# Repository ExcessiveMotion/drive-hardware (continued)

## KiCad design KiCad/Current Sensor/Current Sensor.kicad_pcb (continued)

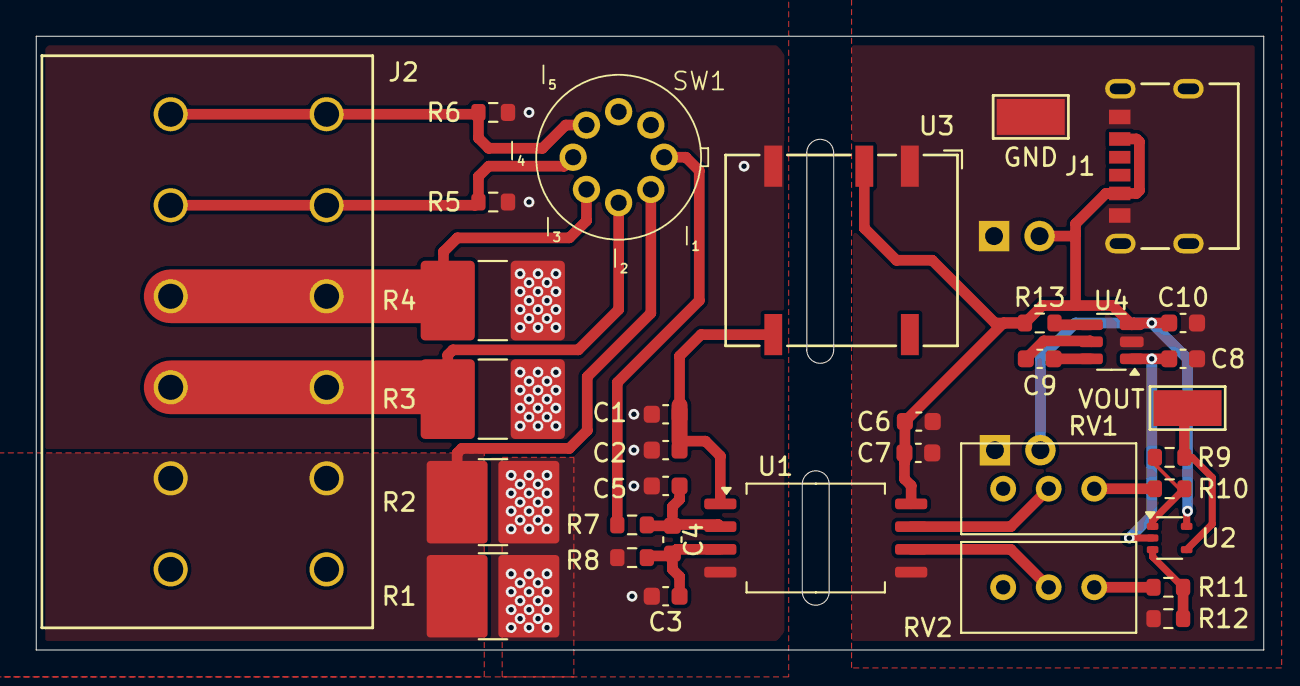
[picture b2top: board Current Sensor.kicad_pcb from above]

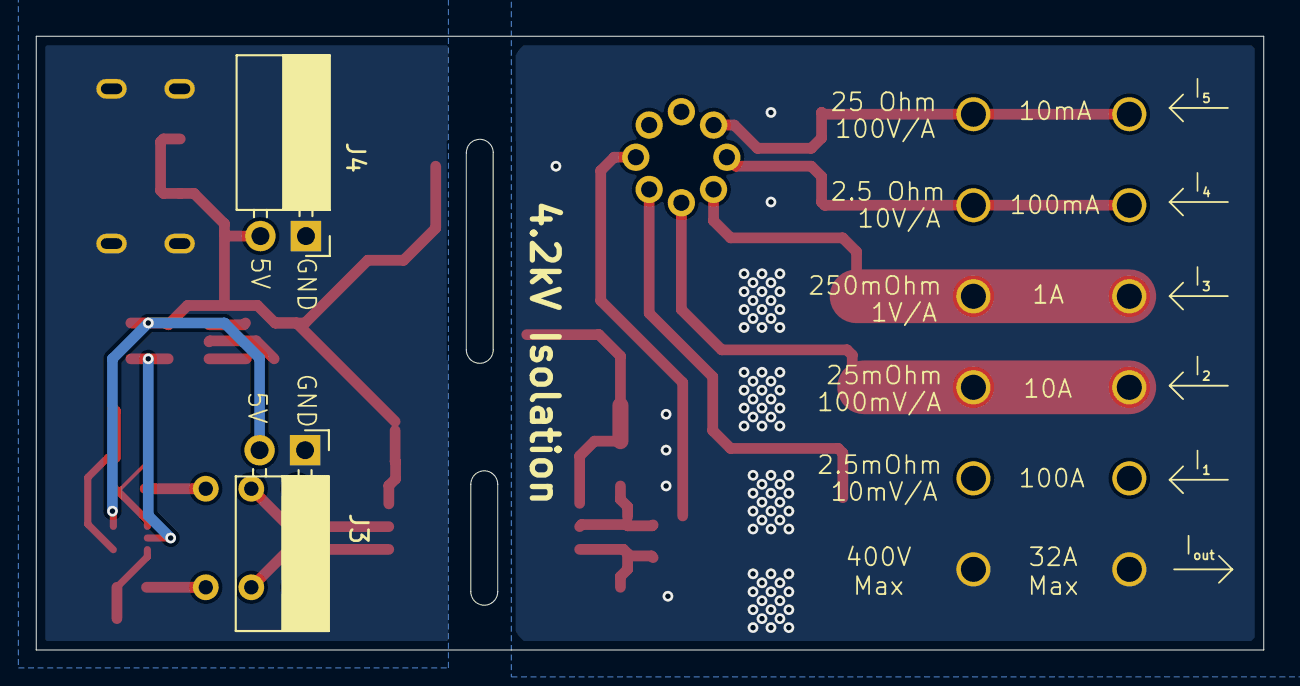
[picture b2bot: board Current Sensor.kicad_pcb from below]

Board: 2 copper layers, 68.5 x 34.2 mm, 36 parts (2 on the bottom side), 23 nets.

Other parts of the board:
GND: TestPoint_Keystone_5019_Minature
J3, J4: PinSocket_1x02_P2.54mm_Horizontal
VOUT: TestPoint_Keystone_5019_Minature

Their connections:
+5V: J3.2, J4.2; also elsewhere on the board
GND2: GND.1, J3.1, J4.1; also elsewhere on the board
VOUT: VOUT.1; also elsewhere on the board

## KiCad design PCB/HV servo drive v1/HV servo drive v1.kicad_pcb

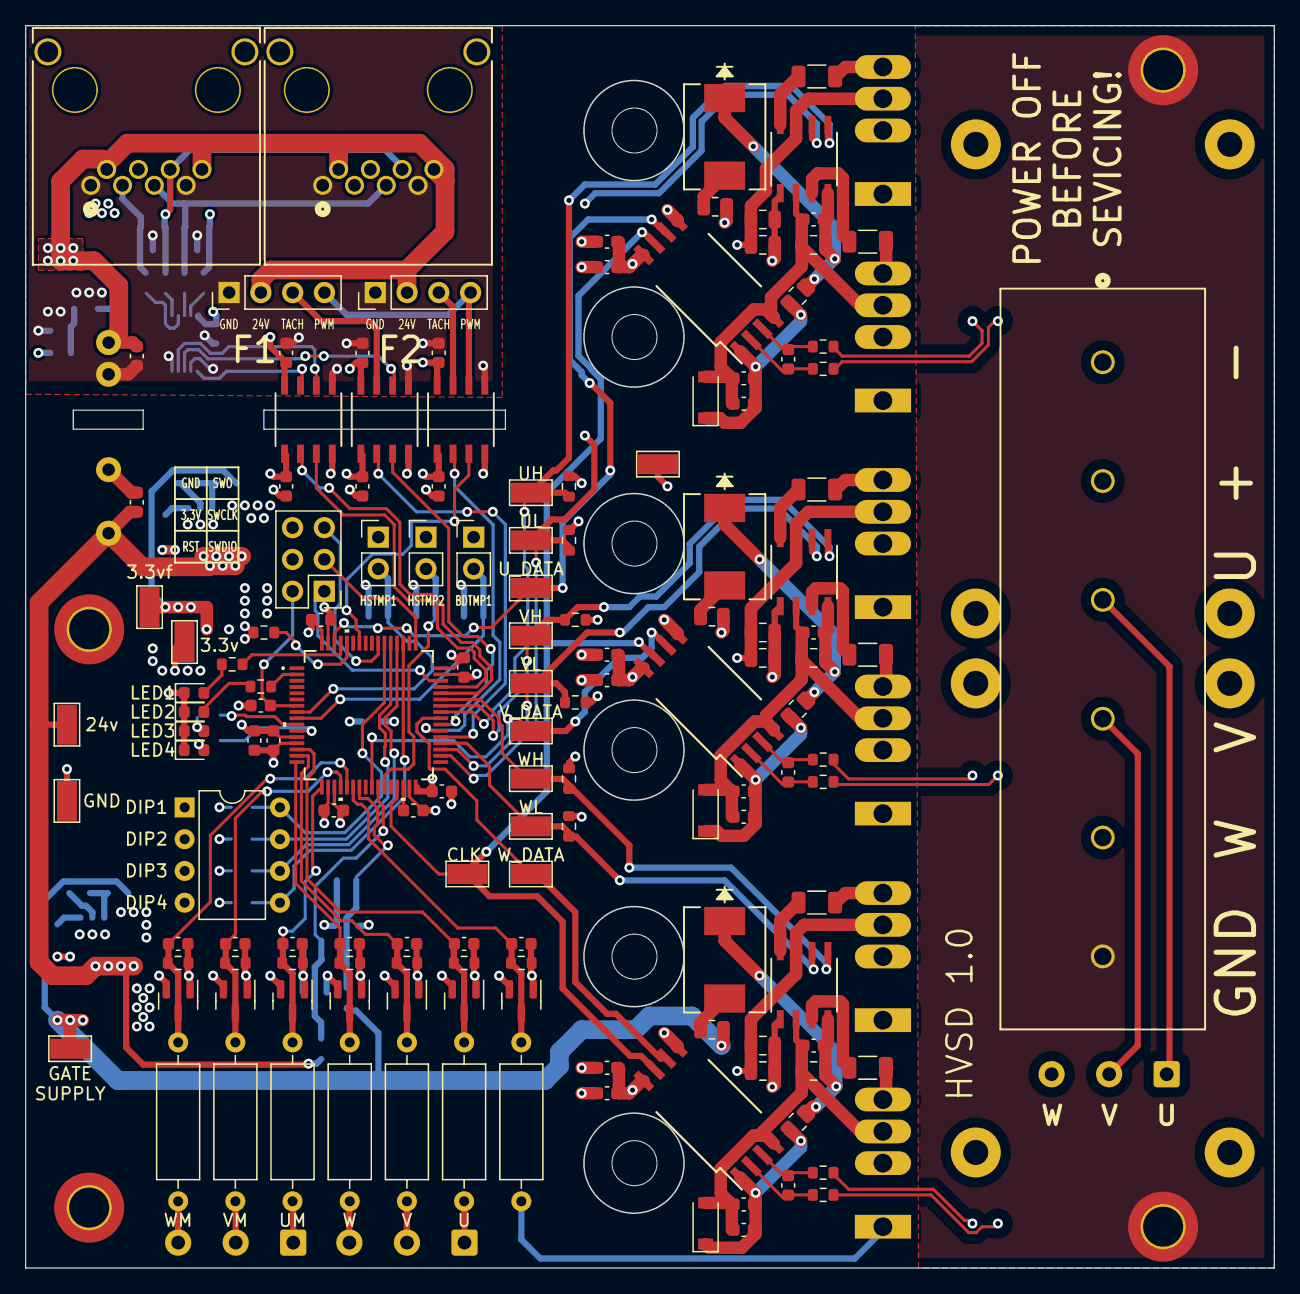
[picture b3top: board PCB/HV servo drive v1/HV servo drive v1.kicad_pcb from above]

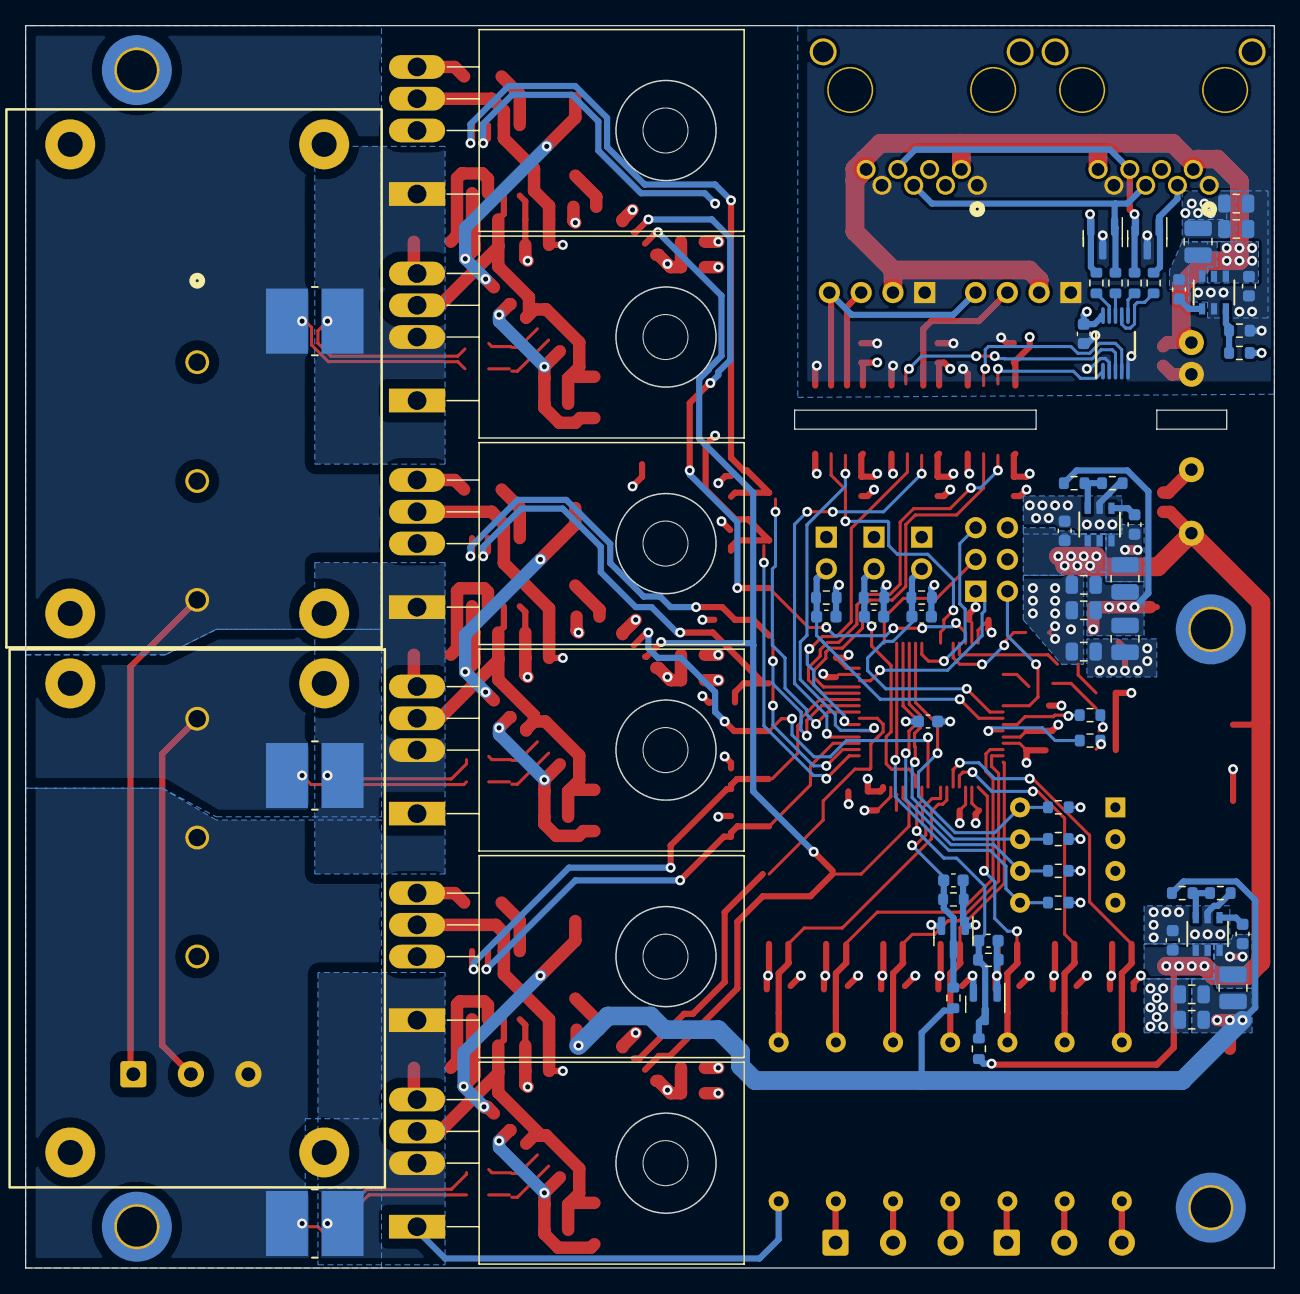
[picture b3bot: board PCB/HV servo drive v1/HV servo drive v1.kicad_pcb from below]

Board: 4 copper layers, 99.8 x 99.3 mm, 221 parts (66 on the bottom side), 125 nets.

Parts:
C1, C2, C3, C4, C5, C6, C7, C14, C15, C17, C20, C21, C26, C28, C29, C30, C31, C33, C34, C35, C36, C50, C51, C56, C59, C61, C63, C68, C69, C70: 0.1uf; C_0603_1608Metric
C8, C9: 40uf; BUS CAP1
C11, C25, C37, C38: .1uf; C_0603_1608Metric
C12, C13, C40, C41, C47, C48, C49: 2.2uf; C_0603_1608Metric
C16, C19, C42, C43, C44, C45, C52, C54, C57: 10uf; C_0805_2012Metric
C18, C22, C23, C24, C27, C32, C39: 1uf; C_0603_1608Metric
C46: ?; C_0805_2012Metric
C53, C55, C58, C60, C62, C64: 22uf; C_0805_2012Metric
C65, C66, C67: 2.2; C_0603_1608Metric
C71, C72, C73: C; C_0603_1608Metric
D1, D2: D_TVS_Dual_AAC; SOT-23
D3, D4, D5, D6: LED; LED_0603_1608Metric
D7, D8, D9, D10, D11, D12, D13, D14, D15: D_Dual_Series_ACK; SOT-23
D16, D17, D18: D; CR_ES3J_ONS
D19, D20, D21: 1N751A; D_SOD-123
H1, H2: MountingHole_Pad; MountingHole_3.2mm_M3_DIN965_Pad_TopBottom
H3, H4: MountingHole; MountingHole_3.2mm_M3_DIN965_Pad_TopBottom
J1, J2: 555153-1; CONN_555153-1_TYC
J3: Conn_02x03_Odd_Even; PinHeader_2x03_P2.54mm_Vertical
J4: OSTYK51104030; CONN04_OSTYK51_40X16P1_OST
J5, J6, J7: Conn_01x03_Female; SolderWire-0.5sqmm_1x03_P4.6mm_D0.9mm_OD2.1mm
L1, L2, L3: 10uH; L_1008_2520Metric
L4: ?; L_1008_2520Metric
M1, M2: Fan_4pin; PinHeader_1x04_P2.54mm_Vertical
NT1, NT2, NT3: NetTie_2; NetTie-2_SMD_Pad0.5mm
Q1, Q2, Q3, Q4, Q5, Q6: C3M0075120K; TO-247-4_Horizontal_TabUp
R1, R2, R3, R4: 10; R_0603_1608Metric
R5: 115k; R_0603_1608Metric
R6, R34, R36: 22.1k; R_0603_1608Metric
R7, R8, R9, R10, R15, R18, R19, R20, R21, R22, R23, R24, R37, R46: 10k; R_0603_1608Metric
R11, R12, R13, R14: 1k; R_0603_1608Metric
R16, R31: 50k; R_0603_1608Metric
R17, R26, R28, R30, R32, R39, R41, R43, R45: 5k; R_0603_1608Metric
R25, R27, R29, R38, R40, R42, R44: 1M; R_Axial_DIN0309_L9.0mm_D3.2mm_P12.70mm_Horizontal
R33: 69.8k; R_0603_1608Metric
R35: 475k; R_0603_1608Metric
R47, R48, R49: 1; R_0805_2012Metric
R50, R51, R56: 800; R_0805_2012Metric
R52, R53, R54, R55, R57, R58: 3; R_1206_3216Metric
R59, R60, R62, R64, R66, R67: R; R_0603_1608Metric
R61, R63, R65: .005; RES_HCSM2818_STP
SW1: SW_DIP_x04; DIP-8_W7.62mm
TH1, TH2, TH3: Thermistor; PinHeader_1x02_P2.54mm_Vertical
TP1, TP2, TP3, TP4, TP5, TP6, TP7, TP8, TP9, TP10, TP11, TP12, TP13, TP14, TP15, TP16: TestPoint; TestPoint_Pad_3.1x1.6mm
U1: THVD1452DGSR; DGS0010A_N
U2, U3, U4: ISO6721BQDRQ1; SOICN-8_LTF
U5: STM32F413RGT6; LQFP64-10x10mm
U6, U8, U9: AP64060QWU-7; IC6_AP64060QWU-7_DIO
U7: CRE1S2412SC; 24v isolated converter
U10, U11, U12: LF2190NTR; SOICN-8_LTF
U13, U14, U15: AMC1306M25DWVR; DWV0008A

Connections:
24V_ISO: C13.1, C18.1, J1.2, J1.8, J2.2, J2.8, M1.2 (+), M2.2 (+), U6.4 (EN), U6.5 (VIN), U7.2 (+VIN)
+3.3V: C5.1, C6.1, C7.1, C14.1, C15.1, C17.1, C20.1, C21.1, C22.1, C24.1, C46.1, C47.1, C48.1, C49.1, C50.1, C51.1, C56.1, D7.2 (K), D8.2 (K), D9.2 (K), D10.2 (K), D11.2 (K), D12.2 (K), D13.2 (K), D14.2 (K), D15.2 (K), J3.4, L4.2, SW1.1, SW1.2, SW1.3, SW1.4, TH1.1, TH2.1, TH3.1, TP13.1, U2.1 (VCC1), U3.1 (VCC1), U4.1 (VCC1), U5.13 (VDDA/VREF+), U5.19 (VDD), U5.32 (VDD), U5.48 (VDD), U5.64 (VDD), U13.8 (DVDD), U14.8 (DVDD), U15.8 (DVDD)
+5V: C1.1, C2.1, C3.1, C4.1, C16.1, C19.1, L1.2, R5.1, U1.10 (VCC), U2.8 (VCC2), U3.8 (VCC2), U4.8 (VCC2)
+15V: C43.1, C45.1, C53.1, C55.1, C58.1, C60.1, C62.1, C64.1, L3.2, R31.1, R35.1, R47.1, R48.1, R49.1, TP7.1, U10.5 (VCC), U11.5 (VCC), U12.5 (VCC)
+24V: C23.1, C40.1, C41.1, R16.1, TP2.1, U7.5 (+VOUT), U8.4 (EN), U8.5 (VIN), U9.4 (EN), U9.5 (VIN)
+VDC: C8.1, C9.1, J4.1, Q1.1 (D), Q3.1 (D), Q5.1 (D), R44.1
-VDC: C8.2, C9.2, J4.2, Q2.2 (S), Q4.2 (S), Q6.2 (S)
BOARD_TEMP_1_ADC: C39.1, R46.1, TH3.2, U5.9 (PC1)
BOOT: R10.1, U5.60 (BOOT0)
CONTROL_SUPPLY_ADC: C26.1, D7.3 (common), R16.2, R17.1, U5.26 (PB0)
DIP_1: R7.1, SW1.8, U5.54 (PD2)
DIP_2: R8.1, SW1.7, U5.53 (PC12)
DIP_3: R9.1, SW1.6, U5.52 (PC11)
DIP_4: R15.1, SW1.5, U5.51 (PC10)
FAN_PWM: U4.3 (INB), U5.58 (PB6)
FAN_PWM_ISO: M1.4 (PWM), M2.4 (PWM), U4.6 (OUTB)
GATE_SUPPLY_ADC: C31.1, D11.3 (common), R31.2, R32.1, U5.23 (PA7)
GND: H1.1, H2.1, J4.6
GND1: C1.2, C2.2, C3.2, C4.2, C13.2, C16.2, C18.2, C19.2, D1.3 (common), D2.3 (common), J1.1, J1.7, J2.1, J2.7, M1.1 (-), M2.1 (-), R6.2, U1.2 (RE_N), U1.5 (GND), U2.5 (GND2), U3.5 (GND2), U4.5 (GND2), U6.2 (GND), U7.1 (-VIN)
GND2: C5.2, C6.2, C7.2, C12.2, C14.2, C15.2, C17.2, C20.2, C21.2, C22.2, C23.2, C24.2, C25.2, C26.2, C27.2, C28.2, C29.2, C30.2, C31.2, C32.2, C33.2, C34.2, C35.2, C36.2, C39.2, C40.2, C41.2, C42.2, C43.2, C44.2, C45.2, C46.2, C47.2, C48.2, C49.2, C50.2, C51.2, C56.2, D3.1 (K), D4.1 (K), D5.1 (K), D6.1 (K), D7.1 (A), D8.1 (A), D9.1 (A), D10.1 (A), D11.1 (A), D12.1 (A), D13.1 (A), D14.1 (A), D15.1 (A), J3.6, NT1.1, NT2.1, NT3.1, R7.2, R8.2, R9.2, R10.2, R15.2, R17.2, R18.2, R19.2, R20.2, R21.2, R22.2, R23.2, R24.2, R26.2, R28.2, R30.2, R32.2, R34.2, R36.2, R37.2, R39.2, R41.2, R43.2, R45.2, R46.2, TP3.1, TP4.1, U2.4 (GND1), U3.4 (GND1), U4.4 (GND1), U5.12 (VSSA/VREF-), U5.18 (VSS), U5.31 (VSS), U5.47 (VSS), U5.63 (VSS), U7.4 (-VOUT), U8.2 (GND), U9.2 (GND), U13.5 (DGND), U14.5 (DGND), U15.5 (DGND)
HEATSINK_TEMP_1_ADC: C27.1, R24.1, TH1.2, U5.27 (PB1)
HEATSINK_TEMP_2_ADC: C32.1, R37.1, TH2.2, U5.8 (PC0)
LED_1: R11.2, U5.61 (PB8)
LED_2: R12.2, U5.2 (PC13)
LED_3: R13.2, U5.10 (PC2)
LED_4: R14.2, U5.11 (PC3)
unnamed: C11.1, U6.1 (BST)
unnamed: C11.2, L1.1, U6.6 (SW)
unnamed: C12.1, U5.30 (VCAP_1)
unnamed: C37.1, U8.1 (BST)
unnamed: C37.2, L2.1, U8.6 (SW)
unnamed: C38.1, U9.1 (BST)
unnamed: C38.2, L3.1, U9.6 (SW)
unnamed: C42.1, C44.1, L2.2, L4.1, R33.1, TP6.1
unnamed: C52.1, C59.1, D16.1 (K), R50.1, U10.8 (VB)
unnamed: C52.2, C59.2, C65.2, C68.2, D19.2 (A), Q1.3 (DS), U10.6 (VS), U13.4 (AGND)
unnamed: C53.2, C60.2, NT1.2, Q2.3 (DS), U10.3 (COM)
unnamed: C54.1, C61.1, D17.1 (K), R51.1, U11.8 (VB)
unnamed: C54.2, C61.2, C66.2, C69.2, D20.2 (A), Q3.3 (DS), U11.6 (VS), U14.4 (AGND)
unnamed: C55.2, C62.2, NT2.2, Q4.3 (DS), U11.3 (COM)
unnamed: C57.1, C63.1, D18.1 (K), R56.1, U12.8 (VB)
unnamed: C57.2, C63.2, C67.2, C70.2, D21.2 (A), Q5.3 (DS), U12.6 (VS), U15.4 (AGND)
unnamed: C58.2, C64.2, NT3.2, Q6.3 (DS), U12.3 (COM)
unnamed: C65.1, C68.1, D19.1 (K), R50.2, U13.1 (AVDD)
unnamed: C66.1, C69.1, D20.1 (K), R51.2, U14.1 (AVDD)
unnamed: C67.1, C70.1, D21.1 (K), R56.2, U15.1 (AVDD)
unnamed: C71.1, R59.2, U13.3 (AINN)
unnamed: C71.2, R64.2, U13.2 (AINP)
unnamed: C72.1, R60.2, U14.3 (AINN)
unnamed: C72.2, R66.2, U14.2 (AINP)
unnamed: C73.1, R62.2, U15.3 (AINN)
unnamed: C73.2, R67.2, U15.2 (AINP)
unnamed: D3.2 (A), R11.1
unnamed: D4.2 (A), R12.1
unnamed: D5.2 (A), R13.1
unnamed: D6.2 (A), R14.1
unnamed: D16.2 (A), R47.2
unnamed: D17.2 (A), R48.2
unnamed: D18.2 (A), R49.2
unnamed: J5.1, R25.1
unnamed: J5.2, R27.1
unnamed: J5.3, R29.1
unnamed: J7.1, R38.1
unnamed: J7.2, R40.1
unnamed: J7.3, R42.1
unnamed: Q1.2 (S), Q2.1 (D), R59.1, R61.1
unnamed: Q1.4 (G), R52.2
unnamed: Q2.4 (G), R53.2
unnamed: Q3.2 (S), Q4.1 (D), R60.1, R63.1
unnamed: Q3.4 (G), R54.2
unnamed: Q4.4 (G), R55.2
unnamed: Q5.2 (S), Q6.1 (D), R62.1, R65.1
unnamed: Q5.4 (G), R57.2
unnamed: Q6.4 (G), R58.2
unnamed: R1.1, U1.9 (A)
unnamed: R2.1, U1.8 (B)
unnamed: R3.1, U1.7 (Z)
unnamed: R4.1, U1.6 (Y)
unnamed: R5.2, R6.1, U6.3 (FB)
unnamed: R33.2, R34.1, U8.3 (FB)
unnamed: R35.2, R36.1, U9.3 (FB)
unnamed: R52.1, U10.7 (HO)
unnamed: R53.1, U10.4 (LO)
unnamed: R54.1, U11.7 (HO)
unnamed: R55.1, U11.4 (LO)
unnamed: R57.1, U12.7 (HO)
unnamed: R58.1, U12.4 (LO)
RESET: C25.1, J3.2, U5.7 (NRST)
RX: U2.2 (OUTA), U5.44 (PA11)
RX+: D1.2 (A2), J1.4, J2.4, R1.2
RX-: D1.1 (A1), J1.5, J2.5, R2.2
RX_ISO: U1.1 (R), U2.7 (INA)
SWCLK: J3.3, U5.49 (PA14)
SWDIO: J3.1, U5.46 (PA13)
SWO: J3.5, U5.55 (PB3)
TACH_1: U3.2 (OUTA), U5.37 (PC6)
TACH_1_ISO: M1.3 (Tacho), U3.7 (INA)
TACH_2: U4.2 (OUTA), U5.38 (PC7)
TACH_2_ISO: M2.3 (Tacho), U4.7 (INA)
TX: U2.3 (INB), U5.45 (PA12)
TX+: D2.2 (A2), J1.6, J2.6, R4.2
TX-: D2.1 (A1), J1.3, J2.3, R3.2
TX_EN: U3.3 (INB), U5.39 (PC8)
TX_EN_ISO: U1.3 (DE), U3.6 (OUTB)
TX_ISO: U1.4 (D), U2.6 (OUTB)
U: J4.3, J6.1, R63.2, R66.1
UH: R18.1, TP8.1, U5.41 (PA8), U11.1 (HIN)
UL: R21.1, TP11.1, U5.34 (PB13), U11.2 (LIN)
UM_ADC: C28.1, D8.3 (common), R25.2, R26.1, U5.17 (PA3)
U_ADC: C33.1, D12.3 (common), R38.2, R39.1, U5.14 (PA0)
U_CLOCK: TP1.1, U5.29 (PB10), U13.7 (CLKIN), U14.7 (CLKIN), U15.7 (CLKIN)
U_DATA: TP15.1, U5.62 (PB9), U14.6 (DOUT)
V: J4.4, J6.2, R61.2, R64.1
VBUS_ADC: C36.1, D15.3 (common), R44.2, R45.1, U5.22 (PA6)
VH: R19.1, TP5.1, U5.42 (PA9), U10.1 (HIN)
VL: R22.1, TP10.1, U5.35 (PB14), U10.2 (LIN)
VM_ADC: C29.1, D9.3 (common), R27.2, R28.1, U5.20 (PA4)
V_ADC: C34.1, D13.3 (common), R40.2, R41.1, U5.15 (PA1)
V_DATA: TP14.1, U5.25 (PC5), U13.6 (DOUT)
W: J4.5, J6.3, R65.2, R67.1
WH: R20.1, TP9.1, U5.43 (PA10), U12.1 (HIN)
WL: R23.1, TP12.1, U5.36 (PB15), U12.2 (LIN)
WM_ADC: C30.1, D10.3 (common), R29.2, R30.1, U5.21 (PA5)
W_ADC: C35.1, D14.3 (common), R42.2, R43.1, U5.16 (PA2)
W_DATA: TP16.1, U5.40 (PC9), U15.6 (DOUT)

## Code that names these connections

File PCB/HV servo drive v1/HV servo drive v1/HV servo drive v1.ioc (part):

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Mcu.Name=STM32F413R(G-H)Tx
Mcu.Package=LQFP64
Mcu.UserName=STM32F413RGTx
PA0.Signal=ADCx_IN0
PA1.Signal=ADCx_IN1
PA10.Signal=S_TIM1_CH3
PA11.Mode=Asynchronous
PA11.Signal=UART4_RX
PA12.Mode=Asynchronous
PA12.Signal=UART4_TX
PA13.Mode=JTAG_5_pins
PA13.Signal=SYS_JTMS-SWDIO
PA14.Mode=JTAG_5_pins
PA14.Signal=SYS_JTCK-SWCLK
PA15.Mode=JTAG_5_pins
PA15.Signal=SYS_JTDI
PA2.Signal=ADCx_IN2
PA3.Signal=ADCx_IN3
PA4.Signal=ADCx_IN4
PA5.Signal=ADCx_IN5
PA6.Signal=ADCx_IN6
PA7.Signal=ADCx_IN7
PA8.Signal=S_TIM1_CH1
PA9.Signal=S_TIM1_CH2
PB0.Signal=ADCx_IN8
PB1.Signal=ADCx_IN9
PB10.Signal=S_CKOUTDFSDM2
PB13.Mode=Output Compare1 CH1 CH1N
PB13.Signal=TIM1_CH1N
PB14.Mode=Output Compare2 CH2 CH2N
PB14.Signal=TIM1_CH2N
PB15.Mode=Output Compare3 CH3 CH3N
PB15.Signal=TIM1_CH3N
PB3.Mode=JTAG_5_pins
PB3.Signal=SYS_JTDO-SWO
PB4.Mode=JTAG_5_pins
PB4.Signal=SYS_JTRST
PB6.Signal=S_TIM4_CH1
PB9.Signal=S_DATAIN1DFSDM2
PC0.Signal=ADCx_IN10
PC1.Signal=ADCx_IN11
PC10.Signal=GPIO_Input
PC11.Signal=GPIO_Input
PC12.Signal=GPIO_Input
PC13.Signal=GPIO_Output
PC14-OSC32_IN.Signal=GPIO_Output
PC15-OSC32_OUT.Signal=GPIO_Output
PC5.Signal=S_DATAIN2DFSDM2
PC6.Signal=S_TIM3_CH1
PC7.Signal=S_TIM3_CH2
PC8.Signal=GPIO_Output
PC9.Signal=S_DATAIN3DFSDM2
PD2.Signal=GPIO_Input
PH0\ -\ OSC_IN.Signal=GPIO_Output
board=custom

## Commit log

2023-09-07 upload of original board and case files
2023-09-10 fix file layout to match other hardware repos
2023-09-11 remove stm32 cubeide project
2023-10-21 main update to v1.1 design
2023-11-20 update board layout
